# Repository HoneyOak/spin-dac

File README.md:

# Spin DAC
A Digital-Analog Converter (DAC) is used for... well, exactly that. Particularly, I want to make a high-quality DAC that converts digital music signals into analog signals for headphones/speakers. Commercial options are quite expensive and big. It is, however, (theoretically) possible to build a budget portable DAC.

This project features a compact, yet high-quality, USB-C DAC, with an inbuilt op-amp. With this, we can acheive significantly better sound quality, with extremely low noise, on any usb-c device.

# Features
- upto 24 bit 192kHz audio
- Ultra Low Noise
- USB-C input
- Seperated Analog and Digital Signals on PCB
- 4 layer PCB to avoid noise and EMI
- 3.5 mm output jack

# Images

## PCB

## CAD

## Schematic

# BOM

**Total price: $94.38**

| name                      | quantity | price          | total | notes                                                | link                                                                                                                                                                                                                                                                                                                     |
| ------------------------- | -------- | -------------- | ----- | ---------------------------------------------------- | ------------------------------------------------------------------------------------------------------------------------------------------------------------------------------------------------------------------------------------------------------------------------------------------------------------------------ |
| USB to I2S Module cm6631a | 1        | 40.82          | 40.82 | cheapest available amazon,                           | [https://www.amazon.com/Generic-CM6631A-Digital-Interface-Converter/dp/B0D47Q1MNB/ref=sr_1_1](https://www.amazon.com/Generic-CM6631A-Digital-Interface-Converter/dp/B0D47Q1MNB/ref=sr_1_1)                                                                                                                               |
| USB C Connector           | 1        | 0.1849710983   | 0.18  |                                                      | [https://electrostoreshop.com/product/type-c-usb-female-to-dip-pcb-breakout-board/](https://electrostoreshop.com/product/type-c-usb-female-to-dip-pcb-breakout-board/)                                                                                                                                                   |
| PCM5102A                  | 1        | 18.26589595    | 18.27 | only available on digikey, so included shipping here | [https://www.digikey.in/en/products/detail/texas-instruments/PCM5102APWR/4341334](https://www.digikey.in/en/products/detail/texas-instruments/PCM5102APWR/4341334)                                                                                                                                                       |
| LDO - LP5907              | 1        | 0.3005780347   | 0.30  |                                                      | [https://www.electronicscomp.com/lp5907mfx-33-nopb-texas-instruments-fixed-ldo-voltage-regulator-22v-to-55v-250mv-dropout-33vout-250maout-sot-23-5](https://www.electronicscomp.com/lp5907mfx-33-nopb-texas-instruments-fixed-ldo-voltage-regulator-22v-to-55v-250mv-dropout-33vout-250maout-sot-23-5)                   |
| Dual Gang Potentiometer   | 1        | 1.398843931    | 1.40  |                                                      | [https://in.rsdelivers.com/product/bourns/ptv112-4420a-b503/bourns-ptv-50k%CF%89-rotary-potentiometer-2-gang-hole/6930702](https://in.rsdelivers.com/product/bourns/ptv112-4420a-b503/bourns-ptv-50k%CF%89-rotary-potentiometer-2-gang-hole/6930702)                                                                     |
| OPA2134PA                 | 1        | 6.523255814    | 6.52  |                                                      | [https://www.digikey.in/en/products/detail/texas-instruments/OPA2134PA/254686](https://www.digikey.in/en/products/detail/texas-instruments/OPA2134PA/254686)                                                                                                                                                             |
| 3.5mm Audio Jack          | 1        | 0.2403468208   | 0.24  |                                                      | [https://sharvielectronics.com/product/audio-jack-3-5mm-trrs-smd/](https://sharvielectronics.com/product/audio-jack-3-5mm-trrs-smd/)                                                                                                                                                                                     |
|                           |          |                |       |                                                      |                                                                                                                                                                                                                                                                                                                          |
| capacitors                |          |                |       |                                                      |                                                                                                                                                                                                                                                                                                                          |
| 1uf                       | 2        | 0.01156069364  | 0.02  | C1,C2                                                | [https://www.ktron.in/product/1uf-50v-ceramic-capacitor-mlcc-smd-0603/?v=c86ee0d9d7ed](https://www.ktron.in/product/1uf-50v-ceramic-capacitor-mlcc-smd-0603/?v=c86ee0d9d7ed)                                                                                                                                             |
| 39nf                      | 2        | 0.2080924855   | 0.42  | C3,C12                                               | [https://www.electronicscomp.com/39nf-50v-smd-capacitor-0603-package?srsltid=AfmBOoq25UC_fSLY1ZbxNZT30KAw-xIDVuQYCKMltO6b1sqZaJZG5aGtvKs](https://www.electronicscomp.com/39nf-50v-smd-capacitor-0603-package?srsltid=AfmBOoq25UC_fSLY1ZbxNZT30KAw-xIDVuQYCKMltO6b1sqZaJZG5aGtvKs)                                       |
| 0.1uf                     | 4        | 0.01156069364  | 0.05  | C4,C7,C8,C15                                         | [https://www.ktron.in/product/100nf-16v-ceramic-capacitor-smd-0603/?v=c86ee0d9d7ed](https://www.ktron.in/product/100nf-16v-ceramic-capacitor-smd-0603/?v=c86ee0d9d7ed)                                                                                                                                                   |
| 2.2uf                     | 2        | 0.02138728324  | 0.04  | C5,C6                                                | [https://www.ktron.in/product/2-2uf-10v-multi-layer-ceramic-capacitor/?v=c86ee0d9d7ed](https://www.ktron.in/product/2-2uf-10v-multi-layer-ceramic-capacitor/?v=c86ee0d9d7ed)                                                                                                                                             |
| 10uf                      | 1        | 0.02138728324  | 0.02  | C9                                                   | [https://www.ktron.in/product/10uf-25v-multi-layered-ceramic-capacitor-2/?v=c86ee0d9d7ed](https://www.ktron.in/product/10uf-25v-multi-layered-ceramic-capacitor-2/?v=c86ee0d9d7ed)                                                                                                                                       |
| 2.2nf                     | 2        | 0.008092485549 | 0.02  | C10,C11                                              | [https://www.ktron.in/product/2-nf-50v-mlcc-x7r-smd-0603-yageo/?v=c86ee0d9d7ed](https://www.ktron.in/product/2-nf-50v-mlcc-x7r-smd-0603-yageo/?v=c86ee0d9d7ed)                                                                                                                                                           |
| 1nf                       | 2        | 0.005549132948 | 0.01  | C13,C14                                              | [https://www.ktron.in/product/1nf-50v-multi-layered-ceramic-capacitor-mlcc-smd-0603/?v=c86ee0d9d7ed](https://www.ktron.in/product/1nf-50v-multi-layered-ceramic-capacitor-mlcc-smd-0603/?v=c86ee0d9d7ed)                                                                                                                 |
|                           |          |                |       |                                                      |                                                                                                                                                                                                                                                                                                                          |
| resistors                 |          |                |       |                                                      |                                                                                                                                                                                                                                                                                                                          |
| 590 Ohm                   | 2        | 0.01156069364  | 0.02  | R1,R4                                                | [https://www.evelta.com/590-ohm-1-0603-thick-film-chip-resistor-0603waf5900t5e/?srsltid=AfmBOopxCBKZi5boQG3cTGVZ1r-1LTR2mo5DkxvwV8afwaDh1EBgeA3HZhE](https://www.evelta.com/590-ohm-1-0603-thick-film-chip-resistor-0603waf5900t5e/?srsltid=AfmBOopxCBKZi5boQG3cTGVZ1r-1LTR2mo5DkxvwV8afwaDh1EBgeA3HZhE)                 |
| 470 Ohm                   | 2        | 0.002543352601 | 0.01  | R2,R3                                                | [https://www.ktron.in/product/resistor-470e-1-10w-1-smd-0603/?v=c86ee0d9d7ed](https://www.ktron.in/product/resistor-470e-1-10w-1-smd-0603/?v=c86ee0d9d7ed)                                                                                                                                                               |
| 499 Ohm                   | 2        | 0.01156069364  | 0.02  | R5,R6                                                | [https://www.evelta.com/499-ohm-1-0603-thick-film-chip-resistor-0603waf4990t5e/?srsltid=AfmBOooC9A-sNrTWw4AAz6qx-uM3zw_H2IjvYKp0OpZFmxF9rxKQU7Fy7LE](https://www.evelta.com/499-ohm-1-0603-thick-film-chip-resistor-0603waf4990t5e/?srsltid=AfmBOooC9A-sNrTWw4AAz6qx-uM3zw_H2IjvYKp0OpZFmxF9rxKQU7Fy7LE)                 |
| 2.49 kOhm                 | 2        | 0.002543352601 | 0.01  | R7,R8                                                | [https://www.ktron.in/product/resistor-2-49k-ohms-1-1-10w-smd-0603-copy/?srsltid=AfmBOop4X3-TdVeo1nzuMWkoKFz_kVAzhG0kxXRbi8xaDZLN0iCi9cbBdN8&v=c86ee0d9d7ed](https://www.ktron.in/product/resistor-2-49k-ohms-1-1-10w-smd-0603-copy/?srsltid=AfmBOop4X3-TdVeo1nzuMWkoKFz_kVAzhG0kxXRbi8xaDZLN0iCi9cbBdN8&v=c86ee0d9d7ed) |
| PCB Fabrication           | 1        | 26.01156069    | 26.01 |                                                      | [https://www.lioncircuits.com](https://www.lioncircuits.com)                                                                                                                                                                                                                                                             |
| TOTAL                     |          |                | 94.38 |                                                      |                                                                                                                                                                                                                                                                                                                          |

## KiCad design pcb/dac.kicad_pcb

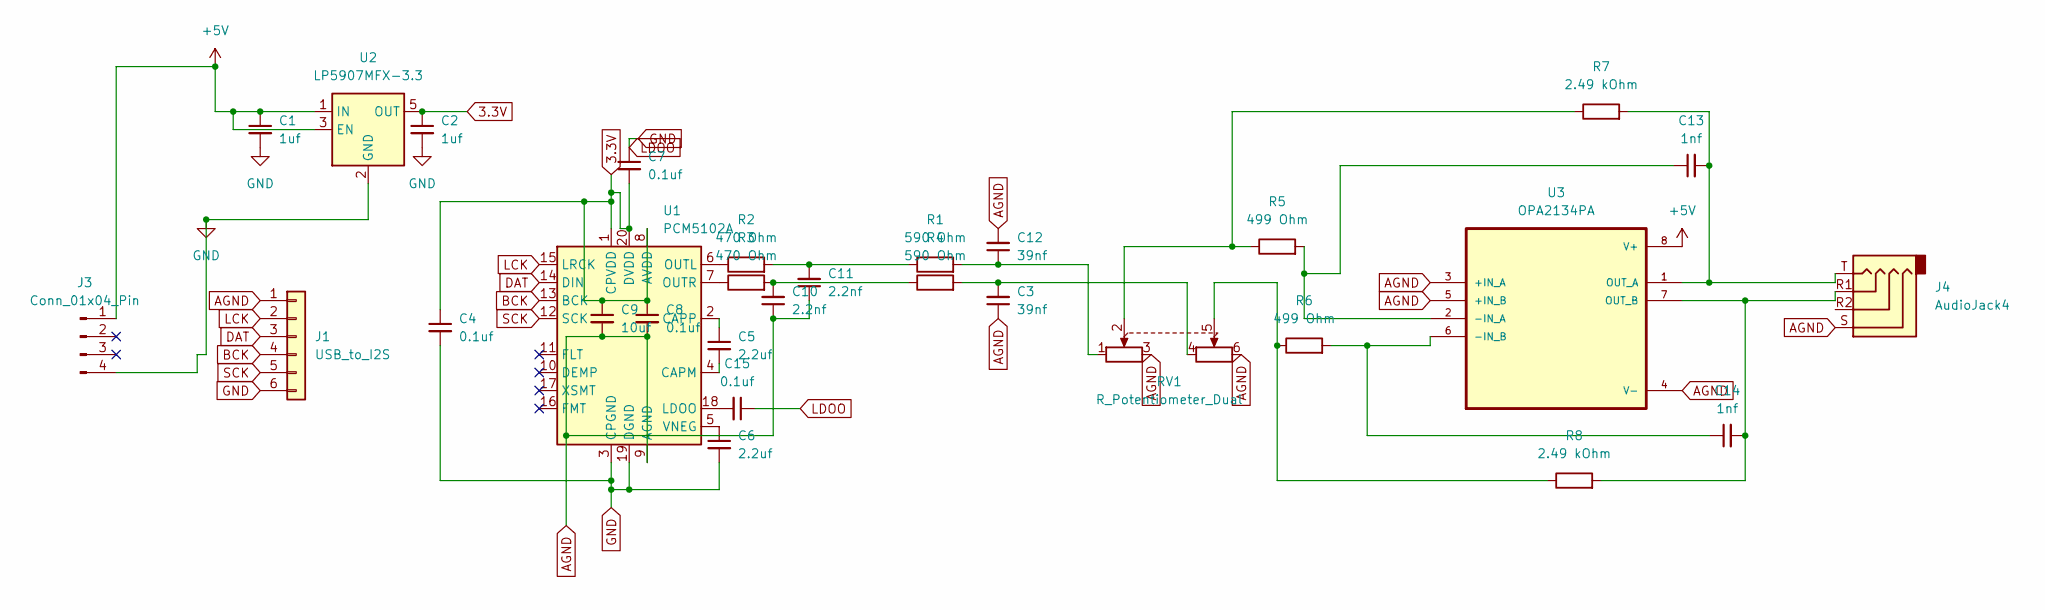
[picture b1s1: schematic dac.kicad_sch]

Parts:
C1, C2: 1uf; C_0201_0603Metric
C3, C12: 39nf; C_0201_0603Metric
C4, C7, C8, C15: 0.1uf; C_0201_0603Metric
C5, C6: 2.2uf; C_0201_0603Metric
C9: 10uf; C_0201_0603Metric
C10, C11: 2.2nf; C_0201_0603Metric
C13, C14: 1nf; C_0201_0603Metric
J1: USB_to_I2S; USB_I2S_Module
J3: Conn_01x04_Pin; PinHeader_1x04_P1.00mm_Vertical
J4: AudioJack4; Jack_3.5mm_KoreanHropartsElec_PJ-320D-4A_Horizontal
R1, R4: 590 Ohm; R_0201_0603Metric
R2, R3: 470 Ohm; R_0201_0603Metric
R5, R6: 499 Ohm; R_0201_0603Metric
R7, R8: 2.49 kOhm; R_0201_0603Metric
RV1: R_Potentiometer_Dual; Dual_Gang_POT
U1: PCM5102A; TSSOP-20_4.4x6.5mm_P0.65mm
U2: LP5907MFX-3.3; SOT-23-5
U3: OPA2134PA; DIP794W45P254L959H508Q8

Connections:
3.3V: C2.1, C4.1, C7.2, C8.1, C9.1, U1.1 (CPVDD), U1.8 (AVDD), U1.20 (DVDD), U2.5 (OUT)
+5V: C1.1, J3.1, U2.1 (IN), U2.3 (EN), U3.8 (V+)
AGND: C3.1, C8.2, C9.2, C10.1, C11.1, C12.2, J1.1, J4.S, RV1.3, RV1.6, U1.9 (AGND), U3.3 (+IN_A), U3.4 (V-), U3.5 (+IN_B)
BCK: J1.4, U1.13 (BCK)
DAT: J1.3, U1.14 (DIN)
GND: C1.2, C2.2, C4.2, C6.2, C7.1, C15.1, J1.6, J3.4, U1.3 (CPGND), U1.19 (DGND), U2.2 (GND)
LCK: J1.2, U1.15 (LRCK)
unnamed: C3.2, R4.2, RV1.4
unnamed: C10.2, R3.2, R4.1
unnamed: C11.2, R1.1, R2.2
unnamed: C12.1, R1.2, RV1.1
unnamed: R5.1, R7.1, RV1.2
unnamed: R6.1, R8.1, RV1.5
unnamed: C5.2, U1.4 (CAPM)
unnamed: C5.1, U1.2 (CAPP)
unnamed: C15.2, U1.18 (LDOO)
unnamed: R2.1, U1.6 (OUTL)
unnamed: R3.1, U1.7 (OUTR)
unnamed: C6.1, U1.5 (VNEG)
unnamed: C13.1, R5.2, U3.2 (-IN_A)
unnamed: C14.1, R6.2, U3.6 (-IN_B)
unnamed: C13.2, J4.T, R7.2, U3.1 (OUT_A)
unnamed: C14.2, J4.R1, R8.2, U3.7 (OUT_B)
SCK: J1.5, U1.12 (SCK)

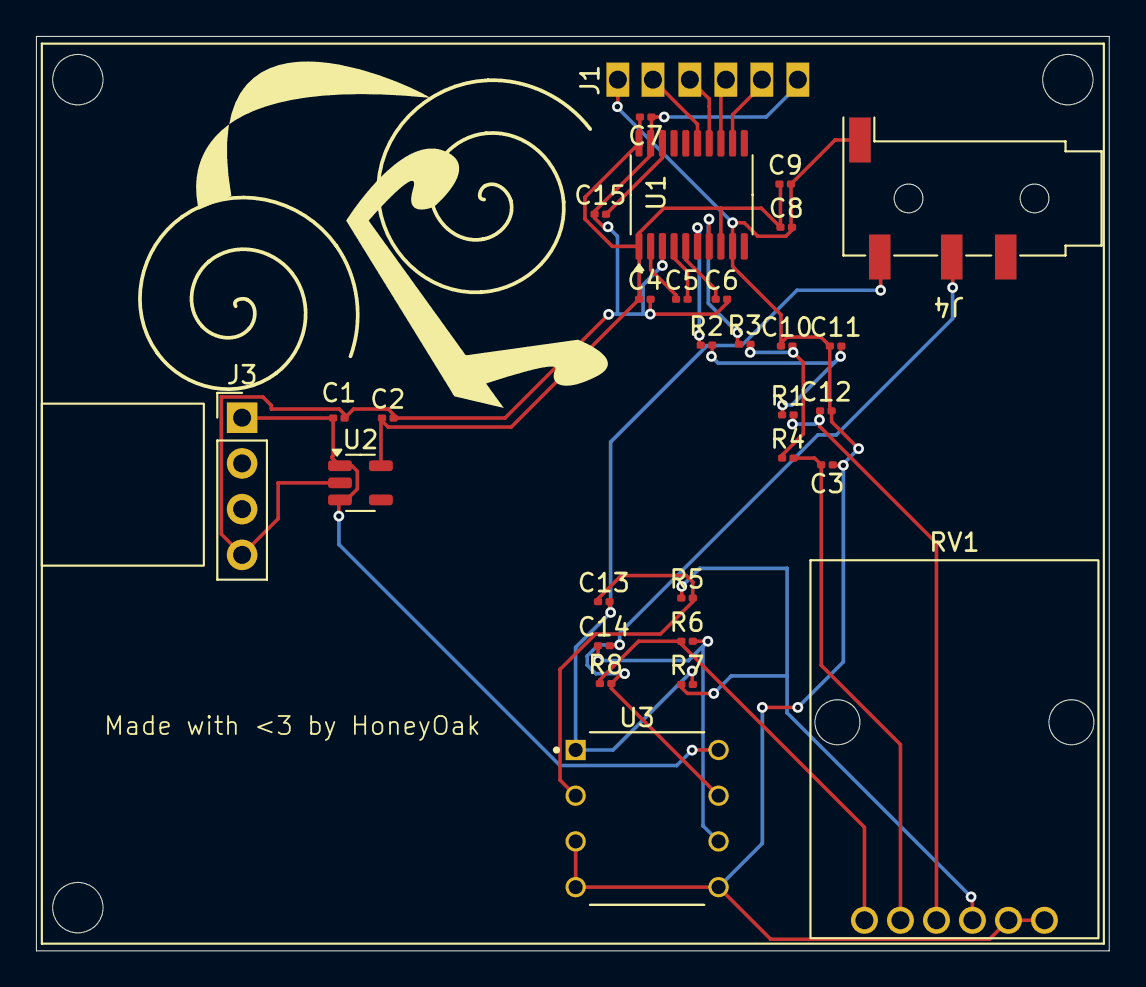
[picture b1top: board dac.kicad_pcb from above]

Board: 2 copper layers, 59.6 x 50.8 mm, 30 parts (0 on the bottom side), 24 nets.

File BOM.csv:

name,quantity,price,total,notes,link
USB to I2S Module cm6631a,1,40.82,40.82,"cheapest available amazon,",https://www.amazon.com/Generic-CM6631A-Digital-Interface-Con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
USB C Connector,1,0.1849710983,0.18,,https://electrostoreshop.com/product/type-c-usb-female-to-di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
PCM5102A,1,18.26589595,18.27,"only available on digikey, so included shipping here",https://www.digikey.in/en/products/detail/texas-instruments/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
LDO - LP5907,1,0.3005780347,0.30,,https://www.electronicscomp.com/lp5907mfx-33-nopb-texas-inst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
Dual Gang Potentiometer,1,1.398843931,1.40,,https://in.rsdelivers.com/product/bourns/ptv112-4420a-b503/b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
OPA2134PA,1,6.523255814,6.52,,https://www.digikey.in/en/products/detail/texas-instruments/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
3.5mm Audio Jack,1,0.2403468208,0.24,,https://sharvielectronics.com/product/audio-jack-3-5mm-trrs-smd/
,,,,,
capacitors,,,,,
1uf,2,0.01156069364,0.02,"C1,C2",https://www.ktron.in/product/1uf-50v-ceramic-capacitor-mlcc-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
39nf,2,0.2080924855,0.42,"C3,C12",https://www.electronicscomp.com/39nf-50v-smd-capacitor-0603-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
0.1uf,4,0.01156069364,0.05,"C4,C7,C8,C15",https://www.ktron.in/product/100nf-16v-ceramic-capacitor-smd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
2.2uf,2,0.02138728324,0.04,"C5,C6",https://www.ktron.in/product/2-2uf-10v-multi-layer-ceramic-c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
10uf,1,0.02138728324,0.02,C9,https://www.ktron.in/product/10uf-25v-multi-layered-ceramic-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
2.2nf,2,0.008092485549,0.02,"C10,C11",https://www.ktron.in/product/2-nf-50v-mlcc-x7r-smd-0603-yage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
1nf,2,0.005549132948,0.01,"C13,C14",https://www.ktron.in/product/1nf-50v-multi-layered-ceramic-c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
,,,,,
resistors,,,,,
590 Ohm,2,0.01156069364,0.02,"R1,R4",https://www.evelta.com/590-ohm-1-0603-thick-film-chip-resist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
470 Ohm,2,0.002543352601,0.01,"R2,R3",https://www.ktron.in/product/resistor-470e-1-10w-1-smd-0603/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
499 Ohm,2,0.01156069364,0.02,"R5,R6",https://www.evelta.com/499-ohm-1-0603-thick-film-chip-resist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
2.49 kOhm,2,0.002543352601,0.01,"R7,R8",https://www.ktron.in/product/resistor-2-49k-ohms-1-1-10w-smd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
PCB Fabrication,1,26.01156069,26.01,,https://www.lioncircuits.com
TOTAL,,,94.38,,

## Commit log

2025-08-05 Update pcb
2025-08-05 update gerbers
